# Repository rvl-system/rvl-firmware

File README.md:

# RVL Firmware

Source code for my RVL system, meant to be run on [RVL Controller Boards](https://github.com/rvl-system/rvl-controller-board). Written using [PlatformIO](http://platformio.org/).

This project is still under heavy development, documentation coming soon once things have settled!

In the mean time, check out this tech demo video of the hardware (as of July 2018).

And a photo of the system on my bike at Burning Man 2017:

And finally a video of an art piece I designed the lighting for at Burning Man 2019

## Notes

The ESP32 sometimes has trouble with Linksys brand routers. If you find that controllers work for a while, then disconnect and never reconnect, try a different router.

# License

All schematics, layouts, software, and other documentation for raver-lights is released under the General Public License.

Copyright (c) Bryan Hughes <bryan@nebri.us>

RVL is free software: you can redistribute it and/or modify
it under the terms of the GNU General Public License as published by
the Free Software Foundation, either version 3 of the License, or
(at your option) any later version.

RVL is distributed in the hope that it will be useful,
but WITHOUT ANY WARRANTY; without even the implied warranty of
MERCHANTABILITY or FITNESS FOR A PARTICULAR PURPOSE.  See the
GNU General Public License for more details.

You should have received a copy of the GNU General Public License
along with RVL.  If not, see <http://www.gnu.org/licenses/>.

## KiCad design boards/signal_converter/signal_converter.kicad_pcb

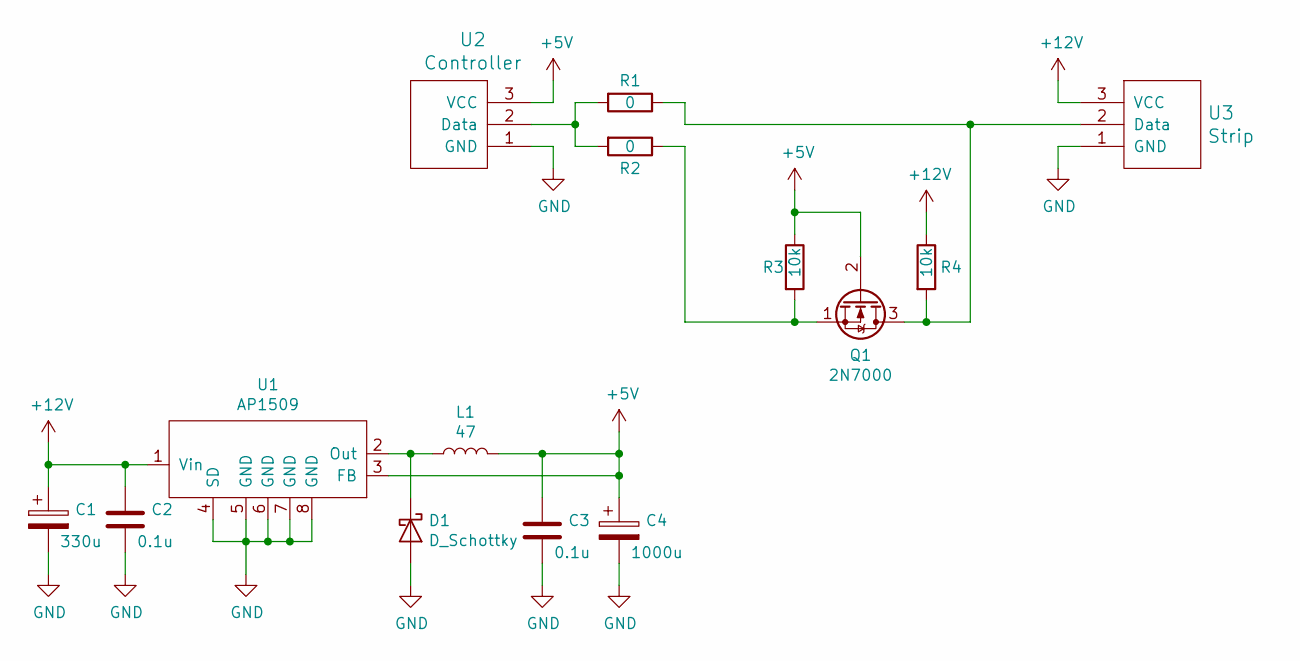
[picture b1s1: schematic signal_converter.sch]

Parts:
C1: 330u; CP_Radial_D8.0mm_P3.50mm
C2, C3: 0.1u; C_0805_2012Metric_Pad1.15x1.40mm_HandSolder
C4: 1000u; CP_Radial_D10.0mm_P5.00mm
D1: D_Schottky; D_SMA
L1: 47; L_0805_2012Metric_Pad1.15x1.40mm_HandSolder
Q1: 2N7000; TO-92_Inline
R1, R2: 0; R_0805_2012Metric_Pad1.15x1.40mm_HandSolder
R3, R4: 10k; R_0805_2012Metric_Pad1.15x1.40mm_HandSolder
U1: AP1509; SOIC-8_3.9x4.9mm_P1.27mm
U2: Controller; PinHeader_1x03_P2.54mm_Vertical
U3: Strip; PinHeader_1x03_P2.54mm_Vertical

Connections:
+5V: C3.1, C4.1, L1.2, Q1.2 (G), R3.1, U1.3 (FB), U2.3 (VCC)
+12V: C1.1, C2.1, R4.1, U1.1 (Vin), U3.3 (VCC)
GND: C1.2, C2.2, C3.2, C4.2, D1.2 (A), U1.4 (SD), U1.5 (GND), U1.6 (GND), U1.7 (GND), U1.8 (GND), U2.1 (GND), U3.1 (GND)
unnamed: D1.1 (K), L1.1, U1.2 (Out)
unnamed: Q1.1 (S), R2.1, R3.2
unnamed: Q1.3 (D), R1.1, R4.2, U3.2 (Data)
unnamed: R1.2, R2.2, U2.2 (Data)

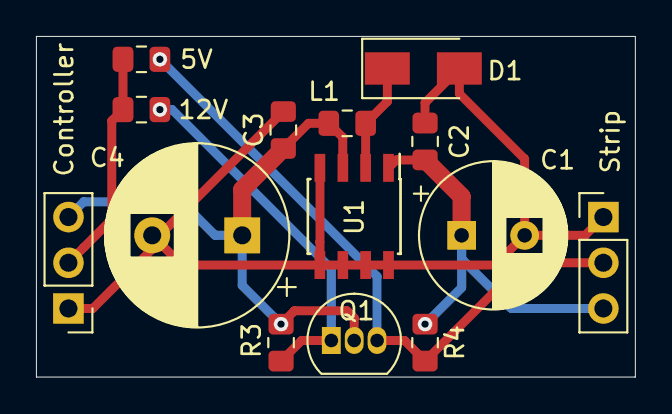
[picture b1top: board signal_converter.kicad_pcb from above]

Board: 2 copper layers, 33.3 x 18.9 mm, 14 parts (0 on the bottom side), 7 nets.

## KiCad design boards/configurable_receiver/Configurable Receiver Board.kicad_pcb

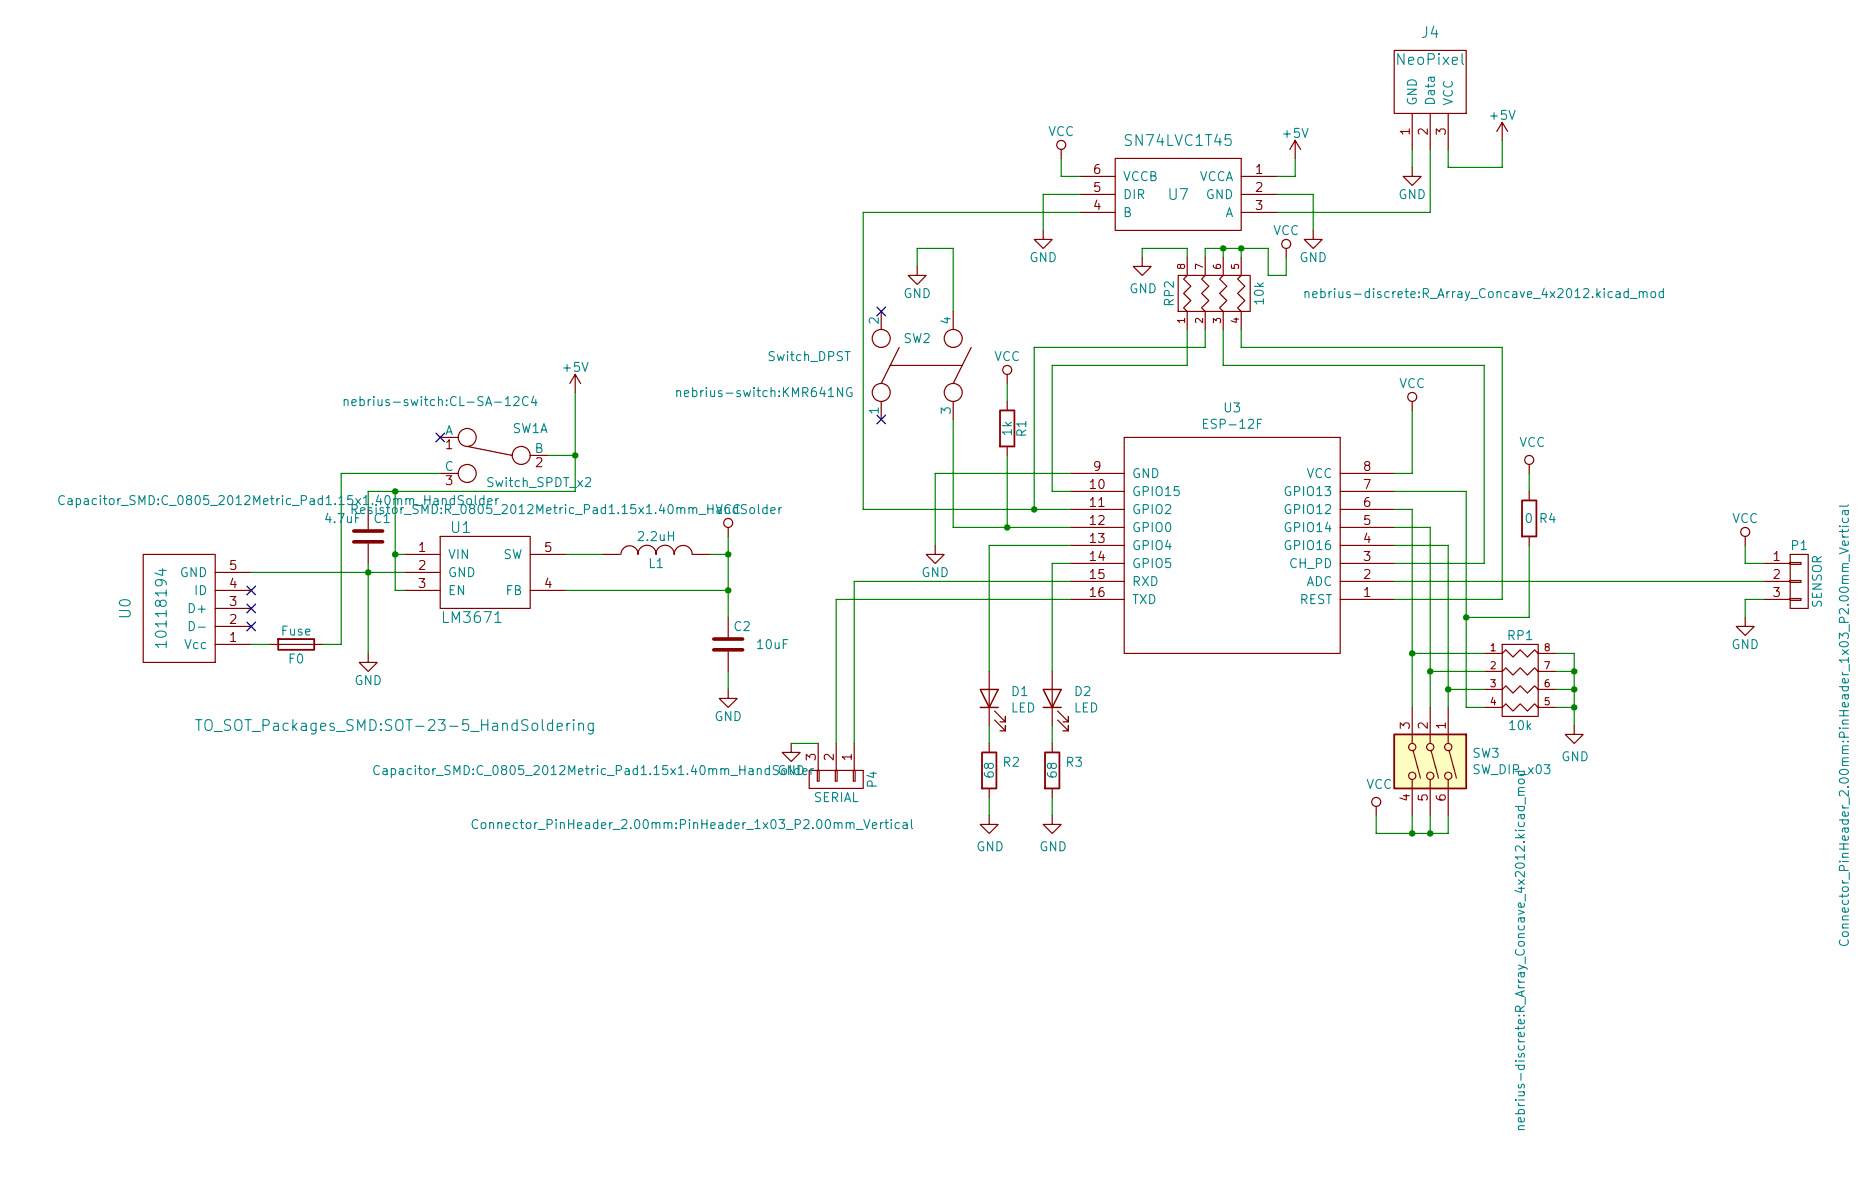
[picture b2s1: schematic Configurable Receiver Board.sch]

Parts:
C1: 4.7uF; C_0805_2012Metric_Pad1.15x1.40mm_HandSolder
C2: 10uF; C_0805_2012Metric_Pad1.15x1.40mm_HandSolder
D1, D2: LED; R_0805_2012Metric_Pad1.15x1.40mm_HandSolder
F0: Fuse; R_0805_2012Metric_Pad1.15x1.40mm_HandSolder
J4: NeoPixel; Pin_Header_Angled_1x03_Pitch2.54mm
L1: 2.2uH; R_0805_2012Metric_Pad1.15x1.40mm_HandSolder
P1: SENSOR; PinHeader_1x03_P2.00mm_Vertical
P4: SERIAL; PinHeader_1x03_P2.00mm_Vertical
R1: 1k; R_0805_2012Metric_Pad1.15x1.40mm_HandSolder
R2, R3: 68; R_0805_2012Metric_Pad1.15x1.40mm_HandSolder
R4: 0; R_0805_2012Metric_Pad1.15x1.40mm_HandSolder
RP1, RP2: 10k; R_Array_Concave_4x2012.kicad_mod
SW1: Switch_SPDT_x2; CL-SA-12C4
SW2: Switch_DPST; KMR641NG
SW3: SW_DIP_x03; SMDIP-6_W9.53mm
U0: 10118194
U1: LM3671; SOT-23-5_HandSoldering
U3: ESP-12F; ESP-12F_SMD
U7: SN74LVC1T45; SOT-23-6_Handsoldering

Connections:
+5V: C1.1, J4.3 (VCC), SW1.2 (B), U1.1 (VIN), U1.3 (EN), U7.1 (VCCA)
GND: C1.2, C2.2, J4.1 (GND), P1.3, P4.3, R2.2, R3.2, RP1.5 (R4), RP1.6 (R3), RP1.7 (R2), RP1.8 (R1), RP2.8 (R1), SW2.4, U0.5 (GND), U1.2 (GND), U3.9 (GND), U7.2 (GND), U7.5 (DIR)
unnamed: D1.1 (K), R2.1
unnamed: D1.2 (A), U3.13 (GPIO4)
unnamed: D2.1 (K), R3.1
unnamed: D2.2 (A), U3.14 (GPIO5)
unnamed: F0.1, SW1.3 (C)
unnamed: F0.2, U0.1 (Vcc)
unnamed: J4.2 (Data), U7.3 (A)
unnamed: L1.1, U1.5 (SW)
unnamed: P1.2, U3.2 (ADC)
unnamed: P4.1, U3.15 (RXD)
unnamed: P4.2, U3.16 (TXD)
unnamed: R1.2, SW2.3, U3.12 (GPIO0)
unnamed: R4.2, RP1.4, U3.7 (GPIO13)
unnamed: RP1.1, SW3.3, U3.6 (GPIO12)
unnamed: RP1.2, SW3.2, U3.5 (GPIO14)
unnamed: RP1.3, SW3.1, U3.4 (GPIO16)
unnamed: RP2.1, U3.10 (GPIO15)
unnamed: RP2.2, U3.11 (GPIO2), U7.4 (B)
unnamed: RP2.3, U3.3 (CH_PD)
unnamed: RP2.4, U3.1 (REST)
VCC: C2.1, L1.2, P1.1, R1.1, R4.1, RP2.5 (R4), RP2.6 (R3), RP2.7 (R2), SW3.4, SW3.5, SW3.6, U1.4 (FB), U3.8 (VCC), U7.6 (VCCB)

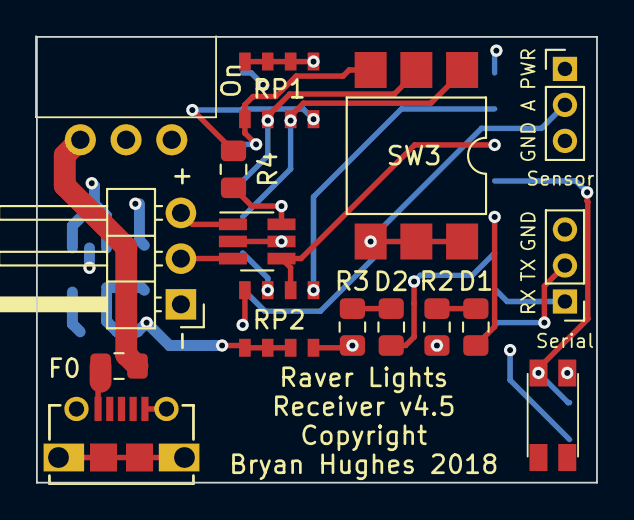
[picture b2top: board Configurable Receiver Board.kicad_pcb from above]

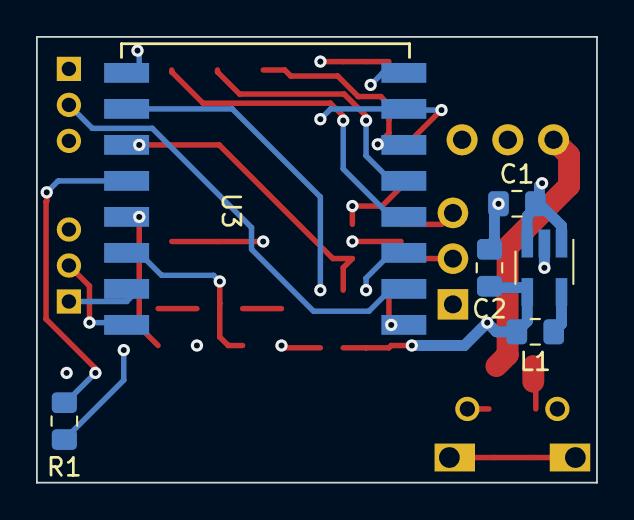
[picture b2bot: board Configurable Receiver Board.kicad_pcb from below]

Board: 4 copper layers, 31.1 x 24.8 mm, 22 parts (6 on the bottom side), 23 nets.

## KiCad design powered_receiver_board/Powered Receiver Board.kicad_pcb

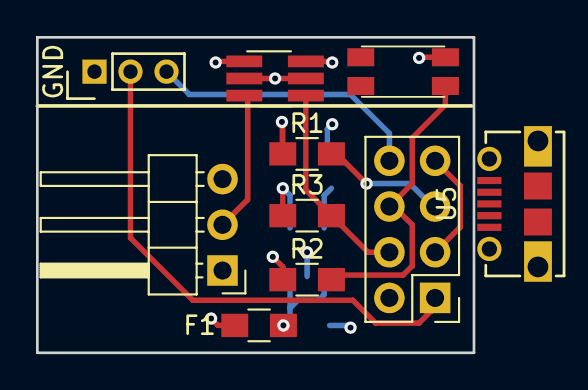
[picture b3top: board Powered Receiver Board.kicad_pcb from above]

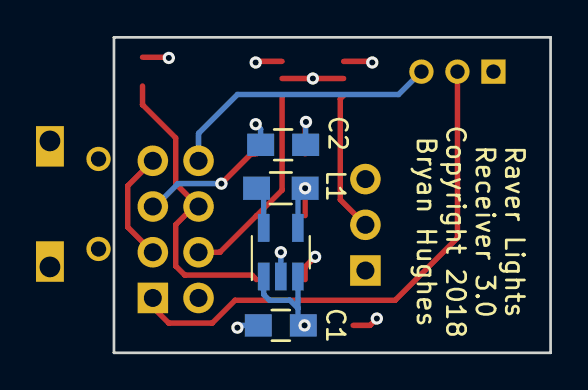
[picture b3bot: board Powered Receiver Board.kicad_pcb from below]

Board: 4 copper layers, 24.3 x 17.5 mm, 14 parts (4 on the bottom side), 11 nets.

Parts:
C1: 4.7uF; C_0805_HandSoldering
C2: 10uF; C_0805_HandSoldering
F1: Fuse; R_0805_HandSoldering
L1: 2.2uH; R_0805_HandSoldering
P4: SERIAL; Pin_Header_Straight_1x03_Pitch2.00mm
R1, R3: 10k; R_0805_HandSoldering
R2: 1k; R_0805_HandSoldering
SW1: SW_DPST; KMR641NG
U1: LM3671; SOT-23-5_HandSoldering
U2: ESP-01; Pin_Header_Straight_2x04_Pitch2.54mm
U3: NeoPixel; Pin_Header_Angled_1x03_Pitch2.54mm
U4: SN74LVC1T45; TSOT-23-6_HandSoldering
U5: 10118194

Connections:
+5V: F1.2, U3.3, U4.1, U5.1
GND: C1.2, C2.2, P4.1, SW1.2, U1.2, U2.2, U3.1, U4.2, U4.5, U5.5
unnamed: C1.1, F1.1, U1.1, U1.3
unnamed: L1.1, U1.5
unnamed: P4.2, U2.1
unnamed: P4.3, U2.8
unnamed: R1.2, U2.5
unnamed: R2.2, SW1.1, U2.6
unnamed: R3.2, U2.4, U4.4
unnamed: U3.2, U4.3
VCC: C2.1, L1.2, R1.1, R2.1, R3.1, U1.4, U2.3, U2.7, U4.6

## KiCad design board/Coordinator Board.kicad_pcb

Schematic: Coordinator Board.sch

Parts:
C1: 4.7uF; C_0805_HandSoldering
C2: 10uF; C_0805_HandSoldering
F0: Fuse; R_0805_HandSoldering
J1, J2, J3, J4: Conn_01x04; Pin_Header_Angled_1x04_Pitch2.54mm
L1: 2.2uH; R_0805_HandSoldering
P4: SERIAL; Pin_Header_Straight_1x03_Pitch2.00mm
R2: 1k; R_0805_HandSoldering
R5, R6: 10k; R_0805_HandSoldering
RP1: 10k; R_Array_Concave_4x2012.kicad_mod
RV1: POT; Model-35-Pot
SW1: Switch_SPDT_x2; CL-SA-12C4
SW2: Switch_DPST; KMR641NG
U0: 10118194
U1: LM3671; SOT-23-5
U3: ESP-12E; ESP-12E_SMD
U4: DIY-OLED-0.96
U5: SF303GJ26
U6: SN74LVC1T45 - MOSI; SOT-23-6_Handsoldering
U7: SN74LVC1T45 - SCLK; SOT-23-6_Handsoldering

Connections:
+3V3: C2.1, L1.2, R2.2, R5.2, R6.1, RP1.4, RV1.3, U1.4 (FB), U3.8, U4.1, U5.5, U6.6, U7.6
+5V: C1.1, J1.1, J2.1, J3.1, J4.1, SW1.2, U1.1 (VIN), U1.3 (EN), U6.1, U7.1
GND: C1.2, C2.2, J1.4, J2.4, J3.4, J4.4, P4.3, RP1.1, RP1.2, RP1.3, RV1.1, SW2.4, U0.5, U1.2 (GND), U3.9, U4.2, U6.2, U6.5, U7.2, U7.5
unnamed: F0.1, SW1.3
unnamed: F0.2, U0.1
unnamed: J1.2, J2.2, J3.2, J4.2, U7.3
unnamed: J1.3, J2.3, J3.3, J4.3, U6.3
unnamed: L1.1, U1.5 (SW)
unnamed: P4.1, U3.15
unnamed: P4.2, U3.16
unnamed: R2.1, SW2.3, U3.12
unnamed: R5.1, U3.3
unnamed: R6.2, U3.1
unnamed: RP1.5, U3.11
unnamed: RP1.6, U3.14, U5.1
unnamed: RP1.7, U3.13, U5.6
unnamed: RP1.8, U3.10, U5.2
unnamed: RV1.2, U3.2
unnamed: U3.4, U4.3
unnamed: U3.5, U7.4
unnamed: U3.6, U4.4
unnamed: U3.7, U6.4

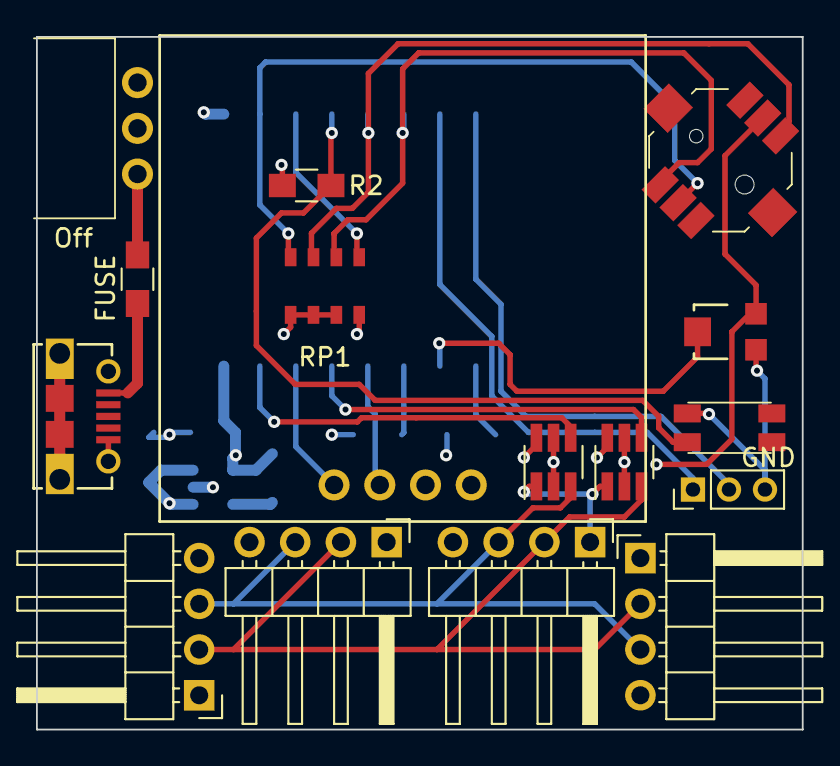
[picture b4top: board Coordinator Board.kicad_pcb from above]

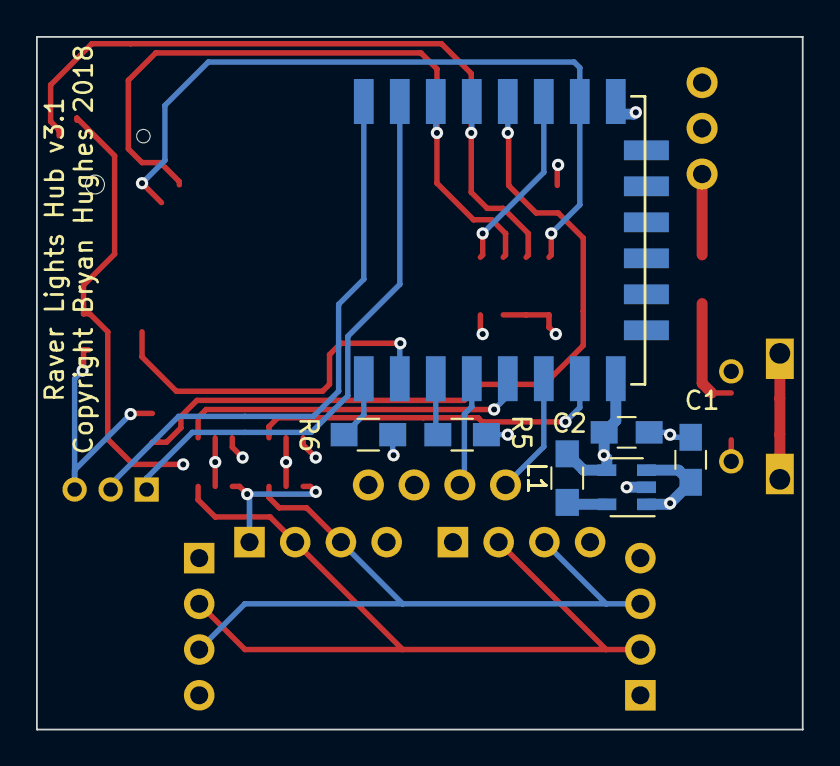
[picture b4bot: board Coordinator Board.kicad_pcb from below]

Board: 4 copper layers, 42.5 x 38.5 mm, 23 parts (7 on the bottom side), 22 nets.

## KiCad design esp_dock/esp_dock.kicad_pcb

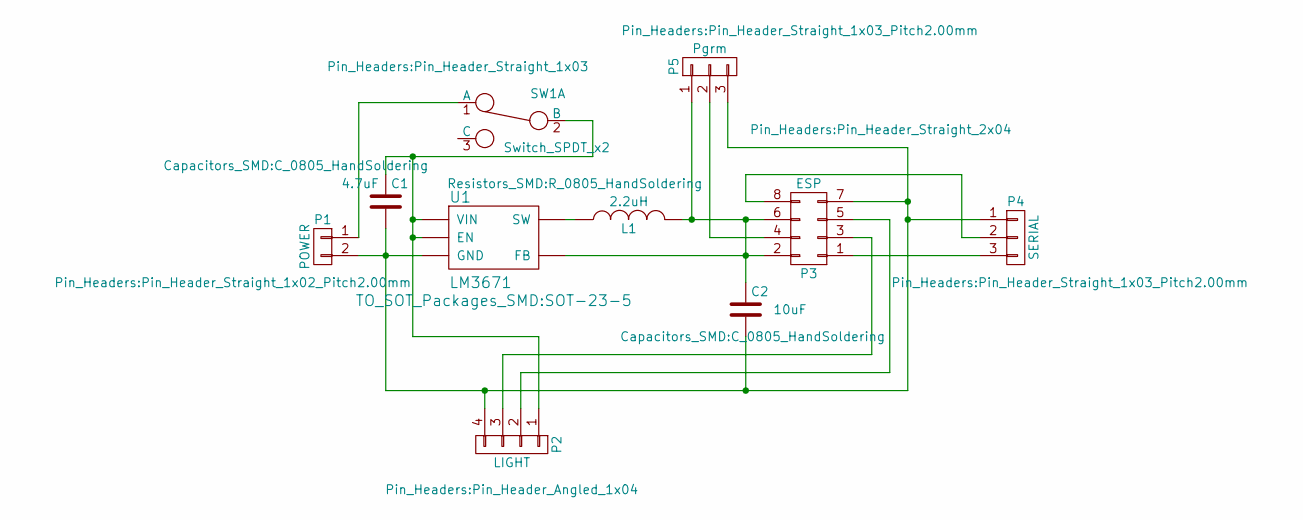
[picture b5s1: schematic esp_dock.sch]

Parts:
C1: 4.7uF; C_0805_HandSoldering
C2: 10uF; C_0805_HandSoldering
L1: 2.2uH; R_0805_HandSoldering
P1: POWER; Pin_Header_Straight_1x02_Pitch2.00mm
P2: LIGHT; Pin_Header_Angled_1x04
P3: ESP; Pin_Header_Straight_2x04
P4: SERIAL; Pin_Header_Straight_1x03_Pitch2.00mm
P5: Pgrm; Pin_Header_Straight_1x03_Pitch2.00mm
SW1: Switch_SPDT_x2; Pin_Header_Straight_1x03
U1: LM3671; SOT-23-5

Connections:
unnamed: C1.1, P2.1, SW1.2 (B), U1.1 (VIN), U1.3 (EN)
unnamed: C1.2, C2.2, P1.2, P2.4, P3.7, P4.1, P5.3, U1.2 (GND)
unnamed: C2.1, L1.2, P3.2, P3.6, P5.1, U1.4 (FB)
unnamed: L1.1, U1.5 (SW)
unnamed: P1.1, SW1.1 (A)
unnamed: P2.2, P3.5
unnamed: P2.3, P3.3
unnamed: P3.1, P4.3
unnamed: P3.4, P5.2
unnamed: P3.8, P4.2

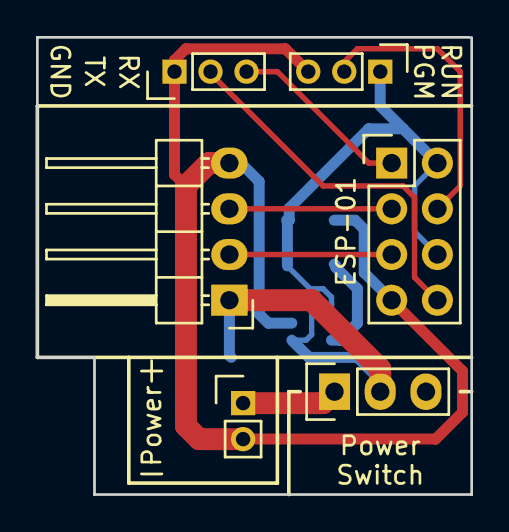
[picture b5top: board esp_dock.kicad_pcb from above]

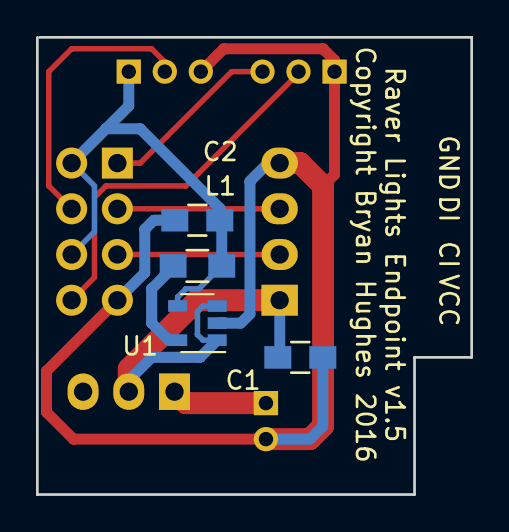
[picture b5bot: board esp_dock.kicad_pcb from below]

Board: 2 copper layers, 24.1 x 25.4 mm, 10 parts (4 on the bottom side), 10 nets.

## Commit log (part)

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2017-03-23 Added rotary encoder to schematic
2017-03-24 Added rotary encoder footprint
2017-04-10 Finished revision of coordinator board
2017-04-10 Added events namespace
2017-06-28 Got the board working (for now, minus encoder)
2017-06-30 Created v2.6 of the coordinator board
2017-07-06 Refactored messaging to use UDP broadcast with a fixed packet
2017-07-06 Got Fade to work with the new broadcast scheme
2017-07-07 Worked in input controls and fixed pulse animations
2017-07-09 v2.7 of the coordinator board
2017-07-09 Timing and code cleanup
2017-07-10 Added the third control axis
2017-07-10 Abstracted animation code out of most files
2017-07-10 Added new animation plus code cleanup
2017-07-10 Added wave animation to the endpoint
2017-07-12 Rewrote the screen code to be more flexible
2017-07-12 Reworked defaults for wave
2017-07-12 Fixed an issue with the copyright notice
2017-08-09 Got the project back up and running on my new machine
2017-08-09 Added common default brightness/preset
2017-08-12 Reworked messaging t be more robust in endpoint
2017-08-16 Fixed an excruciating bug with a frustratingly simply fix
2017-12-30 Removed local components in favor of global submodule
2017-12-30 Relinked footprints
2017-12-31 Finished updated schematic
2018-01-14 Finalized first draft of new schematic
2018-01-14 Created new part layout
2018-01-15 Finished most of the layout
2018-01-26 Revised schematic and added BOM
2018-01-26 Fixed BOM formatting
2018-01-26 Another formatting fix
2018-01-26 Added some better surge protection
2018-01-27 Relaid out parts on board
2018-01-27 Finished first draft of the board
2018-01-28 Board cleanup and DRC fix
2018-01-28 Tweaked silk screen layout
2018-01-28 Merged board directory structure
2018-02-04 Finished and ordered v3.0 of the board!!
2018-02-20 Reworked endpoint code to use default dotstar lib
2018-02-20 Updated through first build
2018-02-20 Initial 3.1 board redesign
2018-02-20 Updated BOM
2018-02-20 Fixed disclaimer
2018-02-20 Slight tweak
2018-02-20 Fixed escaping
2018-02-20 Updated LCD
2018-03-12 Updated r array footprint
2018-03-12 Removed rescue library
2018-03-12 Renamed hub board folder
2018-03-12 Forgot to add unsaved changes
2018-03-20 Restored the endpoint board project
2018-03-20 Updated components
2018-03-20 Cleaned up endpoint board to use newer submodule pattern
2018-03-20 Updated and reverted a whole bunch of changes to use more tried-and-true connections
2018-03-20 Finished redesign, third times the charm?
2018-03-20 Forgot to bump the version number on the silkscreen
2018-03-20 Removed extra silkscreen text
2018-04-04 Revived old Node.js code
2018-04-15 First steps in merging the endpoint and hub code
2018-04-15 Renamed the coordinate code
2018-04-15 Removed jumpers
2018-04-18 Refactored a lot of code
2018-05-05 Pulled in Google’s C++ linter and updated code to pass
2018-05-05 Reorganized messaging and added an indirection
2018-05-05 Added new event listening mechanism
2018-05-05 Removed all old event code
2018-05-05 Removed unused includes
2018-05-05 Refactored the core parts into separate components
2018-05-05 Organized messaging into client/server folders
2018-05-05 Pulled protocol sync out into separate files
2018-05-06 Cleaned up codes
2018-05-07 Reworked event interface
2018-05-07 Fixed bugs, client now works
2018-05-08 Implemented GigglePixel packet infrastructure
2018-05-08 Removed old endpoint code, now that the hub code can do both
2018-05-08 (Re)Added the RPi expansion board
2018-05-08 Added a GigglePixel protocol version guard
2018-05-08 Changed the protocol version after some discussion
2018-05-09 Pulled clock sync out of giggle pixel
2018-05-09 Pulled clock syncing out into a separate packet/system
2018-05-09 Added clock sync to base station codebase
2018-05-10 Minor rearchitecting of state in preparation for palette sharing
2018-05-11 Abstracted out transport
2018-05-12 Switched to using WS2812b LEDs for cost
2018-05-12 Switched to using NeoPixels and other board cleanup
2018-05-12 Bug fixes
2018-05-12 Tweaked interfaces to fix linting errors
2018-05-12 Figured out trick to fixing blinking LEDs (it was interrupts)
2018-05-12 Finished redesigning for WS2812B LEDs
2018-05-13 Updates to work with kitchet raver lights
2018-05-13 First draft of the new receivers
2018-05-14 Added #defines to add more fine-grained control over what’s included
2018-05-14 Revised receiver board
2018-05-14 Added copyright date
2018-05-14 Added BOM and fuse
2018-05-14 Updated BOMs
2018-05-14 BOM tweak
2018-05-16 Switched to using FastLED colorspace
2018-05-16 merged input and screen code into single directory
2018-05-16 Reworked input->screen flow and found the root cause of the freezing bug
2018-05-19 Fixed bug in pulse
2018-05-19 Rewrote screen rendering algorithm
2018-05-20 Refactored where screen values live
2018-05-20 Fixed linter errors
2018-05-20 Rewired buttons
2018-05-20 Fleshed out some UI layout issues
2018-05-20 Added arrows to enums on screen
2018-05-20 Cleaned up screen entries
2018-05-20 Cleaned up icons and added wifi disconnected icon
2018-05-20 Wired in wifi connected state to everything
2018-05-21 Removed obsolete control code
2018-05-21 Reworked structure of controls
2018-05-28 Created a new data bound control mechanism
2018-07-15 Updated base station code to sync properly
2018-07-15 Few other old updates
2018-07-15 Cleaned dist folder
2018-07-15 Wired up mode selection, and it was way easier than I thought
2018-07-15 UI tweaks and bug fixes
2018-07-15 Temporarily removing to fix GitHub image caching bug
2018-07-15 Readding image to force GitHub to flush image cache
2018-07-16 Fleshed out the animation engine in a new "playground" project
2018-07-16 Tweaked angle params to be signed
2018-07-17 Converted part of lighting to the new wave engine
2018-07-17 Finished porting all lights to the new engine
2018-07-17 Got network sync working for new wave engine
2018-07-18 Added loop timing infrastructure to measure performance
2018-07-18 Refactored wave parameters into a single file
2018-07-18 Added a new preset
2018-07-20 Rewrote presets to use cleaner, more centralized architecture
2018-07-20 Fixed some slight README issues
2018-07-27 Implemented a better logging system with levels
2018-08-11 Cleaned up code and got everything working with new base station
2018-08-11 Added systemd service notes
2018-08-20 Fixed some UI bugs
2018-08-20 Made the wave animation more interesting
2018-12-28 Created powered receiver board
2019-01-07 Updated project to new KiCAD format
2019-02-27 Final version of the powered receiver board
2019-03-02 Removed old networking code
2019-03-02 Added infrastructure for new messaging
2019-03-03 Worked in first set of new platform stuff
2019-03-04 Linked in more of RaverLightsMessaging
2019-03-04 It's *really* close to working!
2019-03-04 Finally got it working!
2019-03-14 Updated VS Code C++ properties
2019-03-24 First stab at infrastructure using RVL-ESP
2019-03-24 It's mostly working!
2019-03-25 Added mode update code
2019-03-25 More bug fixes
2019-03-27 Update RVL-ESP
2019-04-22 Reorganized the settings a bit and cleaned some code up
2019-04-23 Brought in updated dependencies
2019-04-23 Created configurable receiver board project
2019-06-06 Restructured and upgraded this repo
2019-06-06 Created v4 of the receiver
2019-06-28 First draft of new channel UI and preset
2019-06-29 Update RVLMessaging
2019-07-09 Bug fixes and polishes
2019-07-09 Set better default brightness
2019-07-10 Got the receiver code working again
2019-07-10 Wired in physical controls
2019-07-10 Reorganized the config a bit
2019-07-10 Refactored to match changes in rvl
2019-07-10 Removed the old base station code, since Home Lights does it waaay better
2019-07-12 Wired in brightness control
2019-07-15 Added WiFi indicator light
2019-07-16 Final updates before DWeb
2019-07-16 Started designing next version of the receiver boards
2019-07-21 Update rvl
2019-07-25 Finished v4.5 of the receiver board
2019-08-06 Wired the clock into the UI
2019-08-07 Simplified the default WiFi passphrase
2019-08-08 Created v1.0 of the signal converter
2019-08-13 Finished RTC support
2019-08-18 Added base station code (again)
2019-08-19 Added configuration support for default mode and remote brightness
2019-09-28 Final BM tweaks
2019-09-28 Added hub2 config
2019-10-04 Added code of conduct
2019-10-04 Moved COPYING to LICENSE
2019-10-29 Removed old submodules
2019-10-29 First steps towards getting the firmware running on the new ESP32 boards
2019-10-29 Forgot to add some files
2019-10-29 Updated submodule
2019-11-04 Minor updates will implementing clock sync
2019-11-04 Wrote access point code
2019-11-12 First step in reworking submodule architecture
2019-11-12 Refactored to match changes in refactored dependencies
2019-11-12 Updated to reflect new clock sync algorithm
2019-11-14 Removed boards and updated submodule links
2019-11-14 Removed outdated and no longer needed base station code
2019-11-14 Moved firmware to the top level
2019-11-14 Removed outdated and not needed files
2019-11-14 Upgraded flash script
2019-12-23 Added support for ESP32 based boards, w/ new flash script
2019-12-23 Added port detection to script
2019-12-24 Got debugging working!
2020-02-23 Removed support for ESP8266 and one-off extensions
2020-02-23 Updated submodules
2020-02-23 Removed old code
2020-02-23 Added performance stats back in
2020-03-03 Started refactor with logging
2020-03-06 Migrated wave settings updated to event based
2020-03-06 Refactored to match removed platform
2020-03-07 Added support for storing settings in flash
2020-03-08 Optimized flash usage
2020-03-08 Added support for saving all settings
2020-04-21 Updated code to match board changes
2020-06-20 Got debugging working on Windows
2020-06-20 Fixed incorrect submodule format
2020-07-02 Added ability to specify WiFi SSID/pass as env vars
2020-07-02 Cleaned up config file
2020-07-02 Got C++ IntelliSense working again on Windows
2020-07-02 Got the old receivers working again
2020-07-07 Started working on tabbed UI
2020-07-08 Got tabs working
2020-07-08 Added system status to tab 2 UI
2020-07-08 Added more status controls
2020-07-20 Updated dependencies
2020-07-27 Updated to match changes in downstream dependencies
2020-08-28 Moved TODO to GitHub issue and updated dependencies
2020-08-29 Updated default preset to use #define
2020-08-29 Set up defaults for bathroom installation
2020-08-29 Added support for remote brightness
2021-06-03 Lint fixes
2021-06-07 Screen entries are now two rows and readable
2021-06-09 Fixed license file naming for GitHub
2021-06-10 Added endRead platform method
2021-06-10 Updated subrepos
2021-06-11 Switched to clang tools for formatting
2021-06-11 More lint work
2021-06-11 I think build is done?
2021-06-12 Settled on a linter style, I think
2021-06-12 Added library checking
2021-06-12 Renamed firmware header files
2021-06-12 builder tweaks
2021-06-12 Custom wrote header linting
2021-06-12 Updated deps
2021-06-15 Added CPATH generation
2021-06-15 Renamed header files to .hpp
2021-06-15 More linting updates
2021-06-15 More linter updates
2021-06-15 More linter fixes
2021-06-16 pio supports compile_commands.json!
2021-06-16 Cleaned up paths
2021-06-16 More cpp config changes
2021-06-16 Yet more linting
2021-06-21 Linting and dep updates
2021-06-21 Temporarily disabled multi-core rendering
2021-06-22 Cleaned up logging
2021-07-20 Added note about linksys routers
2021-09-20 Tuned art-piece parameters
2021-11-15 Made build executable
2021-11-15 Updarted build infrastructure
2021-11-15 Added screen timeout
2021-12-02 Updated rvl lib
2022-06-12 Updraged debugging info and renamed project
2022-06-12 Moved project scripts around
2022-06-13 Wrote script to help debug transient errors
2022-07-31 Fixed an ESP8266 delay bug
2022-07-31 Cleaned up lights file
2022-11-24 Updated deps to get it to compile again
2022-11-25 Added monitor command
2024-06-03 Updated configs
2024-08-20 Added shift animation
2025-02-22 Fixed license statements
2025-07-16 Prepping for new receiver boards
2025-08-03 Implemented new brightness algorithm for receivers
2025-08-03 Implemented status LED for receivers
2025-11-14 Updated dep
2025-11-19 Project cleanup
2025-11-19 Moved multi-threading code into main
2025-11-19 cleanup

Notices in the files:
board/Coordinator Board.kicad_pcb:
Copyright Bryan Hughes 2018
boards/signal_converter/signal_converter.kicad_pcb:
Copyright Bryan Hughes 2019
esp_dock/esp_dock.kicad_pcb:
Copyright Bryan Hughes 2016
powered_receiver_board/Powered Receiver Board.kicad_pcb:
Copyright 2018
